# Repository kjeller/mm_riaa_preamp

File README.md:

# RIAA Preamp (MM)

* Electrical schematic based on [Elliot's design](https://sound-au.com/project06.htm)

* The PCB layout is based on my friend's power supply layout - Hi David :)

Note: It has been tested both with +/-15 and +/-9V supply. 15V fed through the regulators and 2*9V feed from batteries, skipping the power supply.

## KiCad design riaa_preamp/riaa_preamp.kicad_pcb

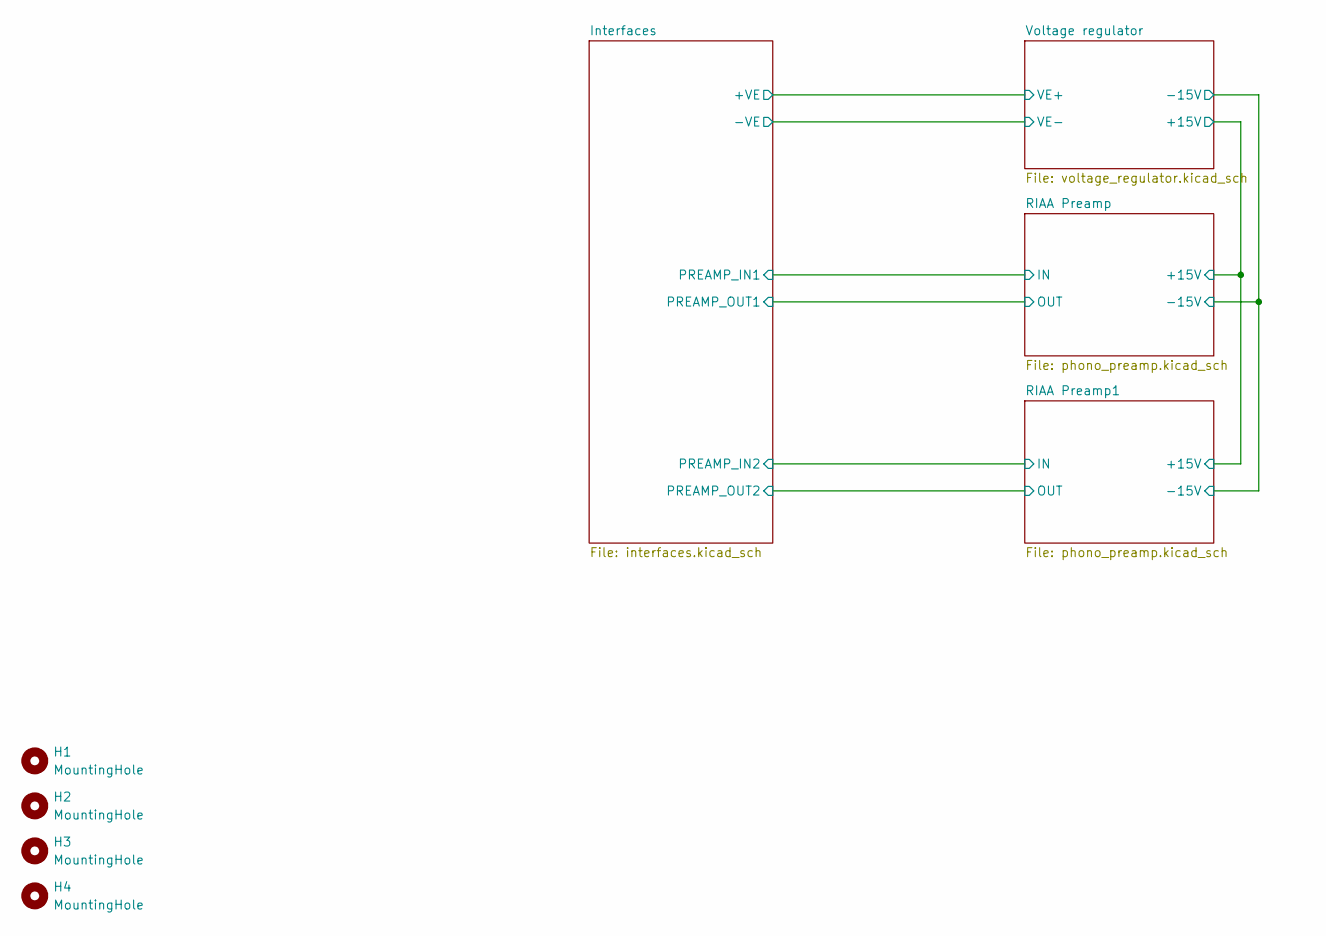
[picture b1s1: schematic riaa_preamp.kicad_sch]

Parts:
H1, H2, H3, H4: MountingHole; MountingHole_4.3mm_M4_DIN965

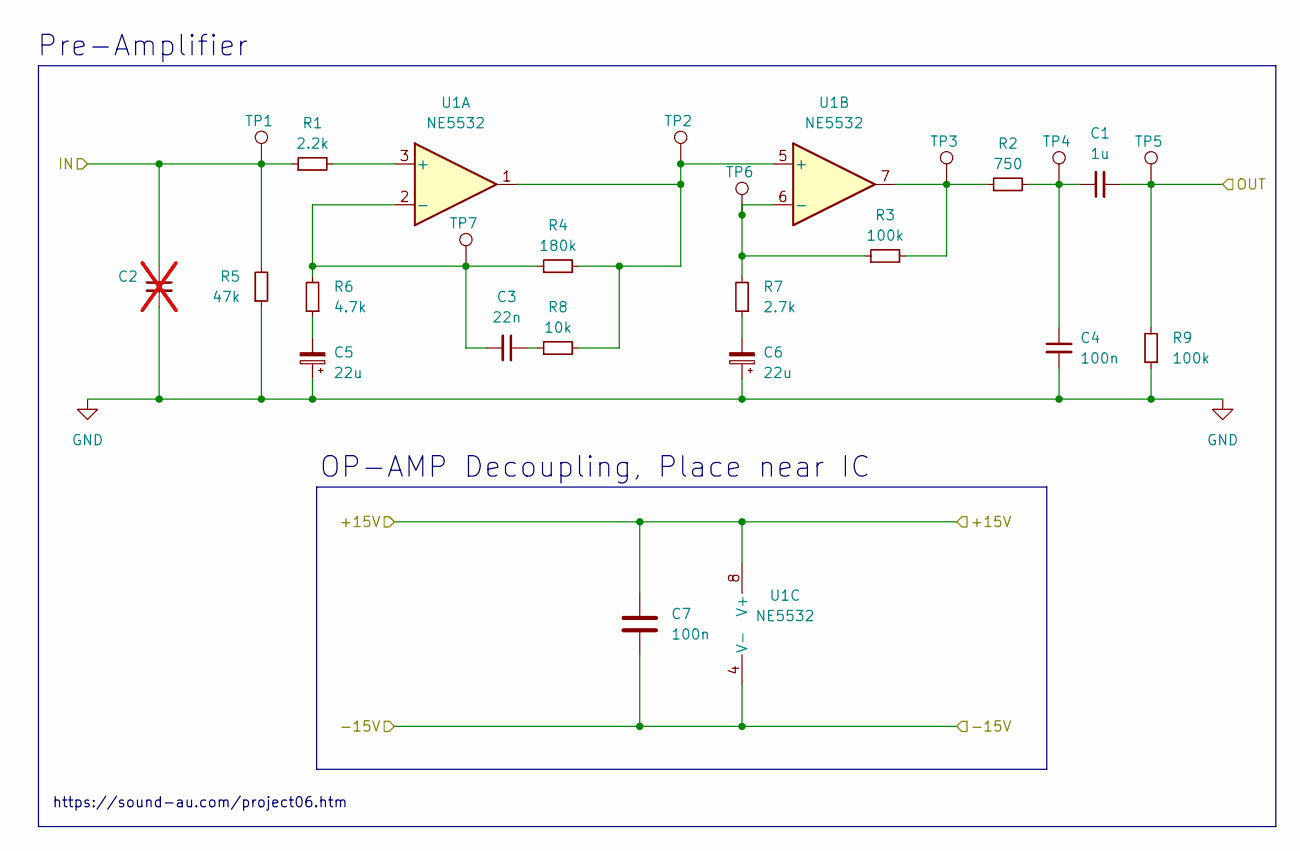
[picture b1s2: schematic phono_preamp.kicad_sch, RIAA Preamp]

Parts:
C1: 1u; C_0603_1608Metric_Pad1.08x0.95mm_HandSolder
C2: C_0603_1608Metric_Pad1.08x0.95mm_HandSolder; not fitted
C3: 22n; C_0603_1608Metric_Pad1.08x0.95mm_HandSolder
C4: 100n; C_0603_1608Metric_Pad1.08x0.95mm_HandSolder
C5, C6: 22u; CP_Radial_D5.0mm_P2.00mm
C7: 100n; C_0603_1608Metric_Pad1.08x0.95mm_HandSolder; Manufacturer Part Numbe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 CL10B104KB8NNNC; JLC C1591
R1: 2.2k; R_0603_1608Metric_Pad0.98x0.95mm_HandSolder
R2: 750; R_0603_1608Metric_Pad0.98x0.95mm_HandSolder
R3, R9: 100k; R_0603_1608Metric_Pad0.98x0.95mm_HandSolder
R4: 180k; R_0603_1608Metric_Pad0.98x0.95mm_HandSolder
R5: 47k; R_0603_1608Metric_Pad0.98x0.95mm_HandSolder
R6: 4.7k; R_0603_1608Metric_Pad0.98x0.95mm_HandSolder
R7: 2.7k; R_0603_1608Metric_Pad0.98x0.95mm_HandSolder
R8: 10k; R_0603_1608Metric_Pad0.98x0.95mm_HandSolder
TP1, TP2, TP3, TP4, TP5, TP6, TP7: TestPoint; TestPoint_THTPad_1.0x1.0mm_Drill0.5mm
U1: NE5532; SOIC-8_3.9x4.9mm_P1.27mm

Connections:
/Interfaces/PREAMP_IN1: C2.1, R1.1, R5.2, TP1.1; also elsewhere on the board
/Interfaces/PREAMP_OUT1: C1.2, R9.2, TP5.1; also elsewhere on the board
/RIAA Preamp/+15V: C7.2, U1.8 (V+); also elsewhere on the board
/RIAA Preamp/-15V: C7.1, U1.4 (V-); also elsewhere on the board
GND: C2.2, C4.2, C5.1, C6.1, R5.1, R9.1; also elsewhere on the board
unnamed: C1.1, C4.1, R2.2, TP4.1
unnamed: C3.1, R8.1
unnamed: C5.2, R6.1
unnamed: C6.2, R7.1
unnamed: R2.1, R3.2, TP3.1, U1.7
unnamed: R1.2, U1.3 (+)
unnamed: C3.2, R4.1, R6.2, TP7.1, U1.2 (-)
unnamed: R4.2, R8.2, TP2.1, U1.1, U1.5 (+)
unnamed: R3.1, R7.2, TP6.1, U1.6 (-)

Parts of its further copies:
C8: 1u; C_0603_1608Metric_Pad1.08x0.95mm_HandSolder
C9: C_0603_1608Metric_Pad1.08x0.95mm_HandSolder; not fitted
C10: 22n; C_0603_1608Metric_Pad1.08x0.95mm_HandSolder
C11: 100n; C_0603_1608Metric_Pad1.08x0.95mm_HandSolder
C12, C13: 22u; CP_Radial_D5.0mm_P2.00mm
C14: 100n; C_0603_1608Metric_Pad1.08x0.95mm_HandSolder; Manufacturer Part Numbe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 CL10B104KB8NNNC; JLC C1591
R10: 2.2k; R_0603_1608Metric_Pad0.98x0.95mm_HandSolder
R11: 750; R_0603_1608Metric_Pad0.98x0.95mm_HandSolder
R12, R18: 100k; R_0603_1608Metric_Pad0.98x0.95mm_HandSolder
R13: 180k; R_0603_1608Metric_Pad0.98x0.95mm_HandSolder
R14: 47k; R_0603_1608Metric_Pad0.98x0.95mm_HandSolder
R15: 4.7k; R_0603_1608Metric_Pad0.98x0.95mm_HandSolder
R16: 2.7k; R_0603_1608Metric_Pad0.98x0.95mm_HandSolder
R17: 10k; R_0603_1608Metric_Pad0.98x0.95mm_HandSolder
TP8, TP9, TP10, TP11, TP12, TP13, TP14: TestPoint; TestPoint_THTPad_1.0x1.0mm_Drill0.5mm
U2: NE5532; SOIC-8_3.9x4.9mm_P1.27mm

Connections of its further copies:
/Interfaces/PREAMP_IN2: C9.1, R10.1, R14.2, TP8.1; also elsewhere on the board
/Interfaces/PREAMP_OUT2: C8.2, R18.2, TP12.1; also elsewhere on the board
/RIAA Preamp/+15V: C14.2, U2.8 (V+); also elsewhere on the board
/RIAA Preamp/-15V: C14.1, U2.4 (V-); also elsewhere on the board
GND: C9.2, C11.2, C12.1, C13.1, R14.1, R18.1; also elsewhere on the board
unnamed: C10.1, R17.1
unnamed: C8.1, C11.1, R11.2, TP11.1
unnamed: C12.2, R15.1
unnamed: C13.2, R16.1
unnamed: R11.1, R12.2, TP10.1, U2.7
unnamed: R10.2, U2.3 (+)
unnamed: C10.2, R13.1, R15.2, TP14.1, U2.2 (-)
unnamed: R13.2, R17.2, TP9.1, U2.1, U2.5 (+)
unnamed: R12.1, R16.2, TP13.1, U2.6 (-)

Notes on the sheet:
Pre-Amplifier
https://sound-au.com/project06.htm
OP-AMP Decoupling, Place near IC

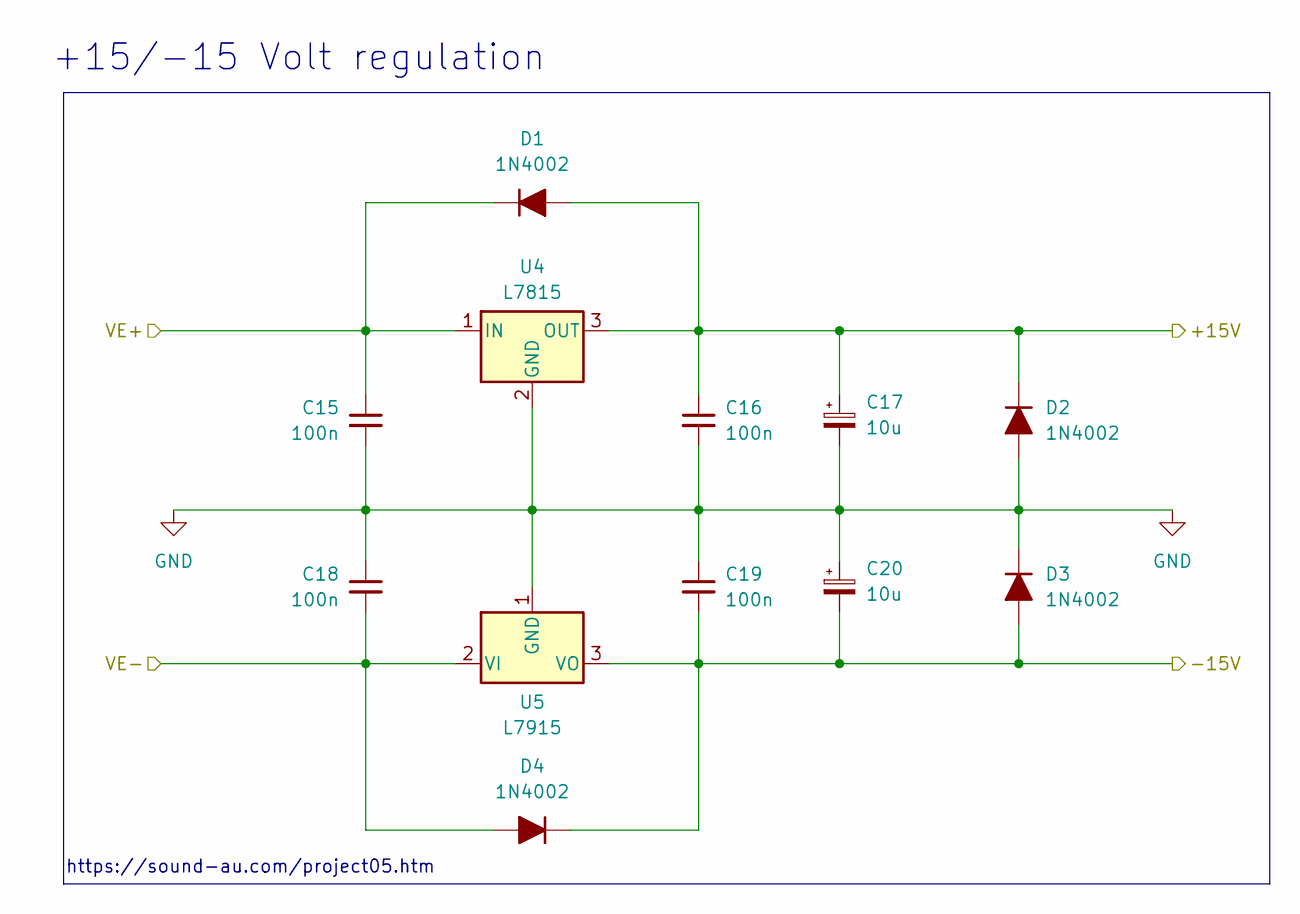
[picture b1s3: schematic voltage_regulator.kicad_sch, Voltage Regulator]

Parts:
C15, C16, C18, C19: 100n; C_0603_1608Metric_Pad1.08x0.95mm_HandSolder
C17, C20: 10u; CP_Radial_D5.0mm_P2.00mm
D1, D2, D3, D4: 1N4002; D_SOD-123F
U4: L7815; TO-220-3_Horizontal_TabUp
U5: L7915; TO-220-3_Horizontal_TabUp

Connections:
/Interfaces/+VE: C15.1, D1.1 (K), U4.1 (IN); also elsewhere on the board
/Interfaces/-VE: C18.2, D4.2 (A), U5.2 (VI); also elsewhere on the board
/RIAA Preamp/+15V: C16.1, C17.1, D1.2 (A), D2.1 (K), U4.3 (OUT); also elsewhere on the board
/RIAA Preamp/-15V: C19.2, C20.2, D3.2 (A), D4.1 (K), U5.3 (VO); also elsewhere on the board
GND: C15.2, C16.2, C17.2, C18.1, C19.1, C20.1, D2.2 (A), D3.1 (K), U4.2 (GND), U5.1 (GND); also elsewhere on the board

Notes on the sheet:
+15/-15 Volt regulation
https://sound-au.com/project05.htm

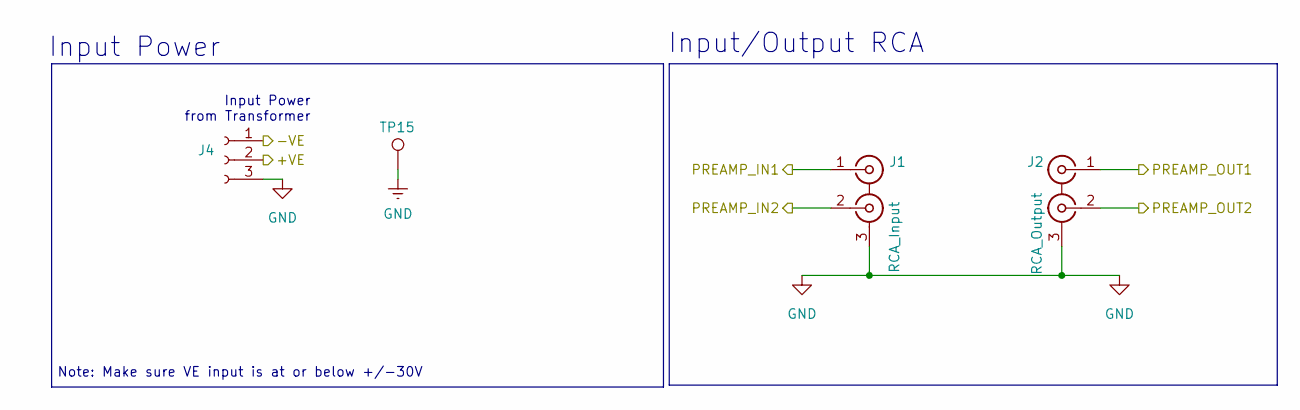
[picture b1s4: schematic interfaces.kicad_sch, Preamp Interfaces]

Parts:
J1: RCA_Input; RCJ-01_Stereo
J2: RCA_Output; RCJ-01_Stereo
J4: Conn_01x03_Socket; JST_EH_B3B-EH-A_1x03_P2.50mm_Vertical
TP15: TestPoint; TestPoint_THTPad_1.0x1.0mm_Drill0.5mm

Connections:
/Interfaces/+VE: J4.2; also elsewhere on the board
/Interfaces/-VE: J4.1; also elsewhere on the board
/Interfaces/PREAMP_IN1: J1.1 (IN1); also elsewhere on the board
/Interfaces/PREAMP_IN2: J1.2 (IN2); also elsewhere on the board
/Interfaces/PREAMP_OUT1: J2.1 (IN1); also elsewhere on the board
/Interfaces/PREAMP_OUT2: J2.2 (IN2); also elsewhere on the board
GND: J1.3 (EXT), J2.3 (EXT), J4.3, TP15.1; also elsewhere on the board

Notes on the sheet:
Input Power
Input Power from Transformer
Note: Make sure VE input is at or below +/-30V
Input/Output RCA

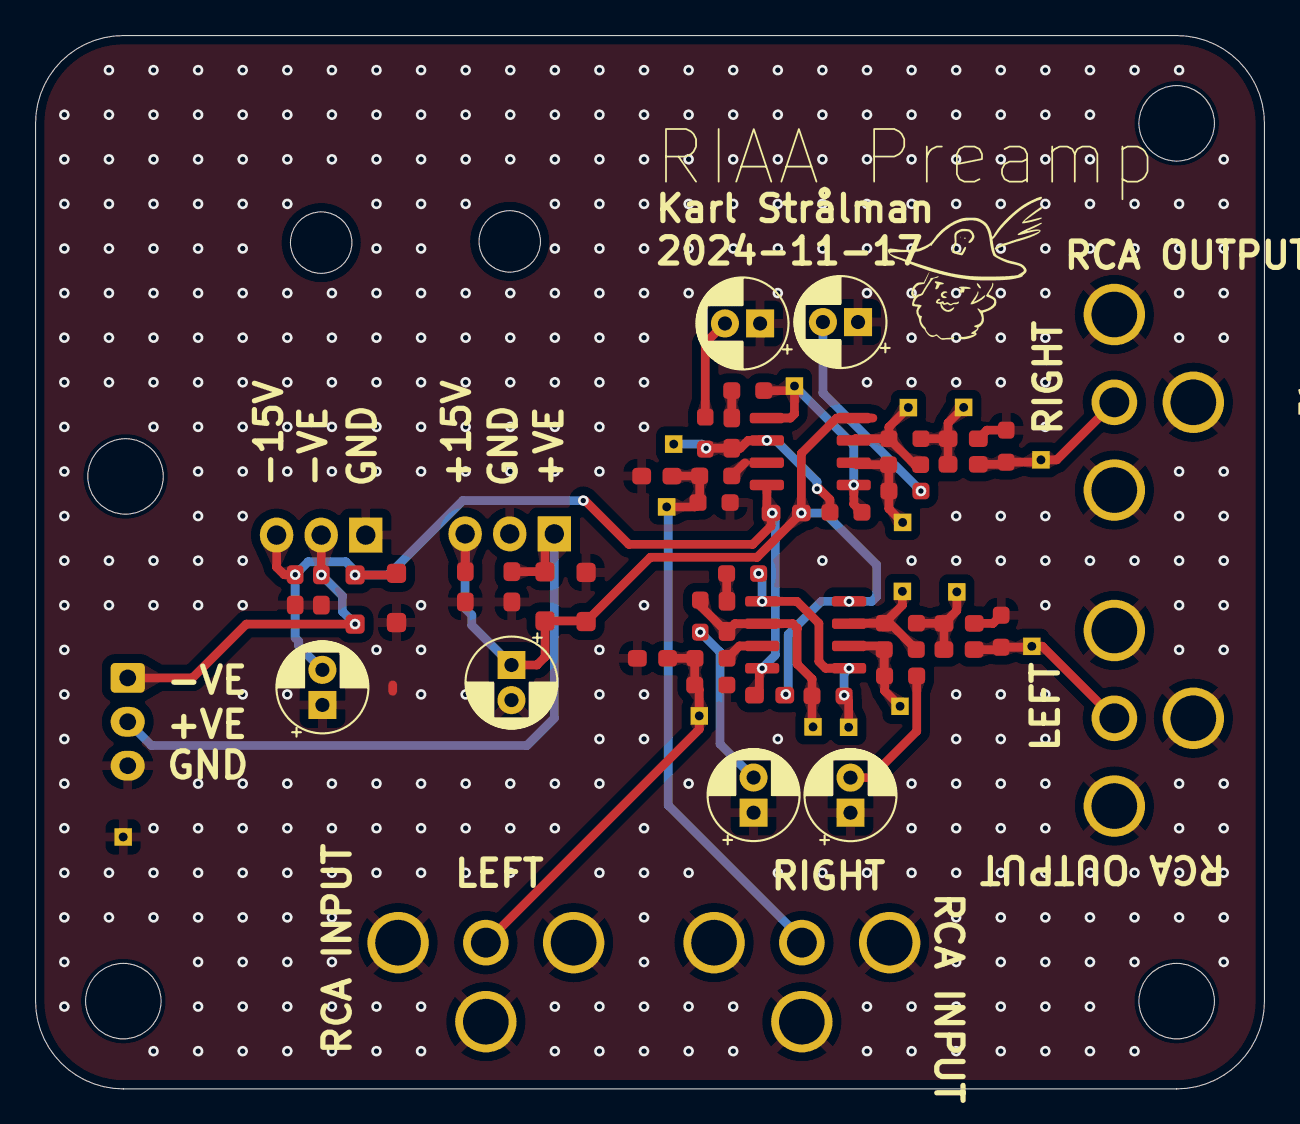
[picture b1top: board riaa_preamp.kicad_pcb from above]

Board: 2 copper layers, 70.0 x 60.0 mm, 68 parts (0 on the bottom side), 27 nets.

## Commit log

2024-12-24 Add gitignore
2024-12-24 Add first version of RIAA preamp
2024-12-24 Add readme
2025-01-10 Fix link in README
